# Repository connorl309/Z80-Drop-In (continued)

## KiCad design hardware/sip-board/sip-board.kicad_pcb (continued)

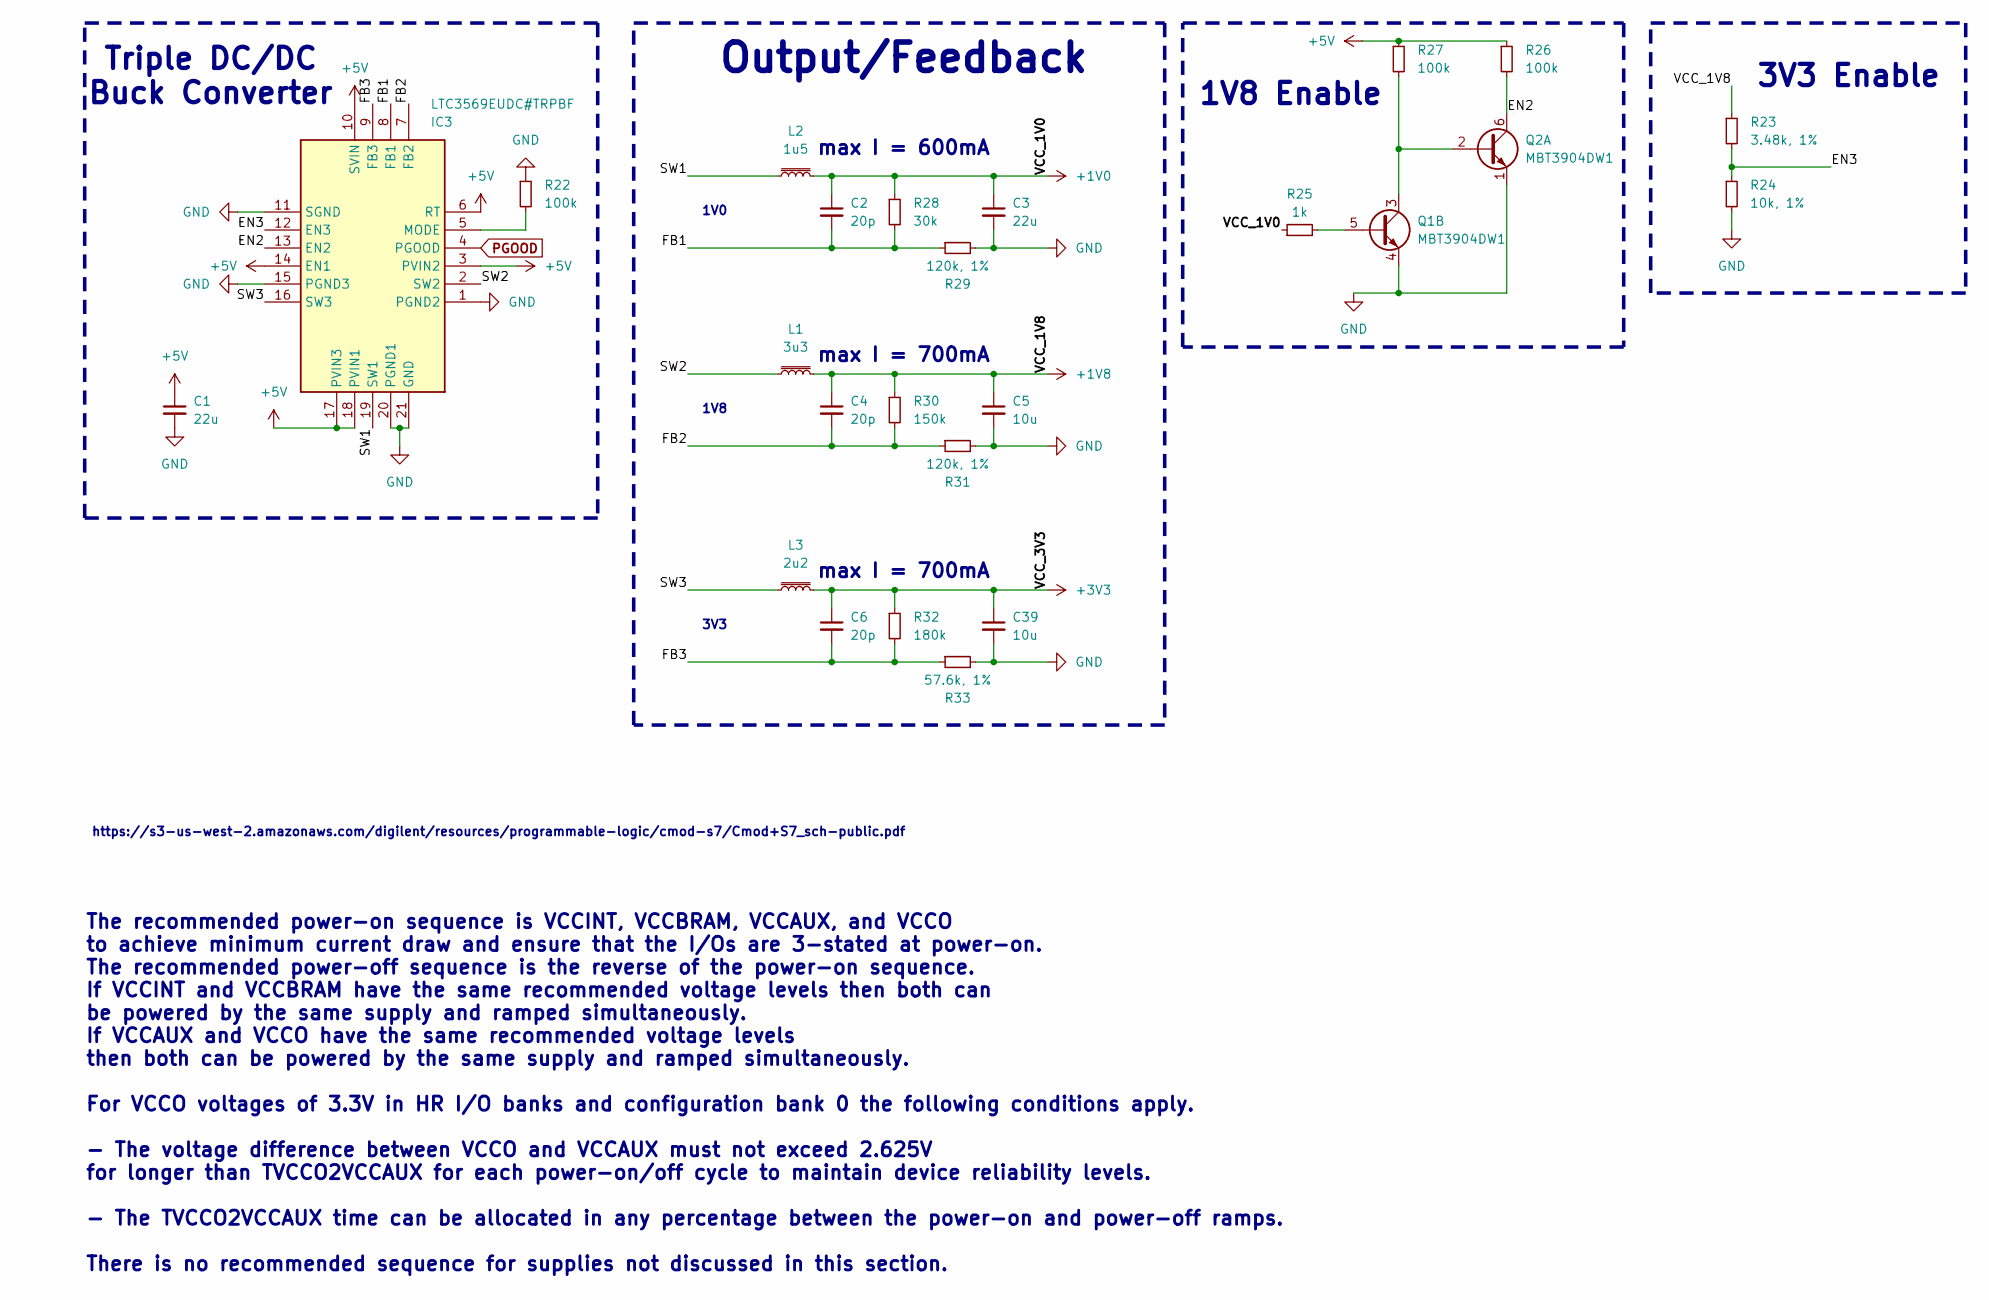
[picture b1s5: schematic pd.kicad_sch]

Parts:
C1, C3: 22u; C_0201_0603Metric
C2, C4, C6: 20p; C_0201_0603Metric
C5, C39: 10u; C_0201_0603Metric
IC3: LTC3569EUDC#TRPBF; QFN50P300X400X80-21N-D; Mouser Part Number 584-LTC3569EUDCTRPBF
L1: 3u3; L_0805_2012Metric; MPN BRC2012T3R3MD
L2: 1u5; L_0805_2012Metric; MPN SRN2012-1R5M
L3: 2u2; L_0805_2012Metric; MPN SRN2012-2R2M
Q1, Q2: MBT3904DW1; SOT-363_SC-70-6
R22, R26, R27: 100k; R_0201_0603Metric
R23: 3.48k, 1%; R_0201_0603Metric
R24: 10k, 1%; R_0201_0603Metric
R25: 1k; R_0201_0603Metric
R28: 30k; R_0201_0603Metric
R29, R31: 120k, 1%; R_0201_0603Metric
R30: 150k; R_0201_0603Metric
R32: 180k; R_0201_0603Metric
R33: 57.6k, 1%; R_0201_0603Metric

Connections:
+1V0: C2.1, C3.1, L2.2, R25.1, R28.1; also elsewhere on the board
+1V8: C4.1, C5.1, L1.2, R23.1, R30.1; also elsewhere on the board
+3V3: C6.1, C39.1, L3.2, R32.1; also elsewhere on the board
+5V: C1.1, IC3.3 (PVIN2), IC3.6 (RT), IC3.10 (SVIN), IC3.14 (EN1), IC3.17 (PVIN3), IC3.18 (PVIN1), R26.1, R27.1; also elsewhere on the board
/Voltage Regulators - 3V3, 1V8, 1V0/EN2: IC3.13 (EN2), Q2.6 (C1), R26.2
/Voltage Regulators - 3V3, 1V8, 1V0/EN3: IC3.12 (EN3), R23.2, R24.1
/Voltage Regulators - 3V3, 1V8, 1V0/FB1: C2.2, IC3.8 (FB1), R28.2, R29.1
/Voltage Regulators - 3V3, 1V8, 1V0/FB2: C4.2, IC3.7 (FB2), R30.2, R31.1
/Voltage Regulators - 3V3, 1V8, 1V0/FB3: C6.2, IC3.9 (FB3), R32.2, R33.1
/Voltage Regulators - 3V3, 1V8, 1V0/SW1: IC3.19 (SW1), L2.1
/Voltage Regulators - 3V3, 1V8, 1V0/SW2: IC3.2 (SW2), L1.1
/Voltage Regulators - 3V3, 1V8, 1V0/SW3: IC3.16 (SW3), L3.1
GND: C1.2, C3.2, C5.2, C39.2, IC3.1 (PGND2), IC3.11 (SGND), IC3.15 (PGND3), IC3.20 (PGND1), IC3.21 (GND), Q1.4 (E2), Q2.1 (E1), R22.1, R24.2, R29.2, R31.2, R33.2; also elsewhere on the board
unnamed: IC3.5 (MODE), R22.2
unnamed: Q1.5 (B2), R25.2
unnamed: Q1.3 (C2), Q2.2 (B1), R27.2
PGOOD: IC3.4 (PGOOD); also elsewhere on the board

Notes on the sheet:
3V3 Enable
max I = 700mA
3V3
Triple DC/DC Buck Converter
The recommended power-on sequence is VCCINT, VCCBRAM, VCCAUX, and VCCO to achieve minimum current draw and ensure that the I/Os are 3-stated at power-on. The recommended power-off sequence is the reverse of the power-on sequence. If VCCINT and VCCBRAM have the same recommended voltage levels then b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
1V0
max I = 600mA
1V8
https://s3-us-west-2.amazonaws.com/digilent/resources/programmable-logic/cmod-s7/Cmod+S7_sch-public.pdf
Output/Feedback
1V8 Enable

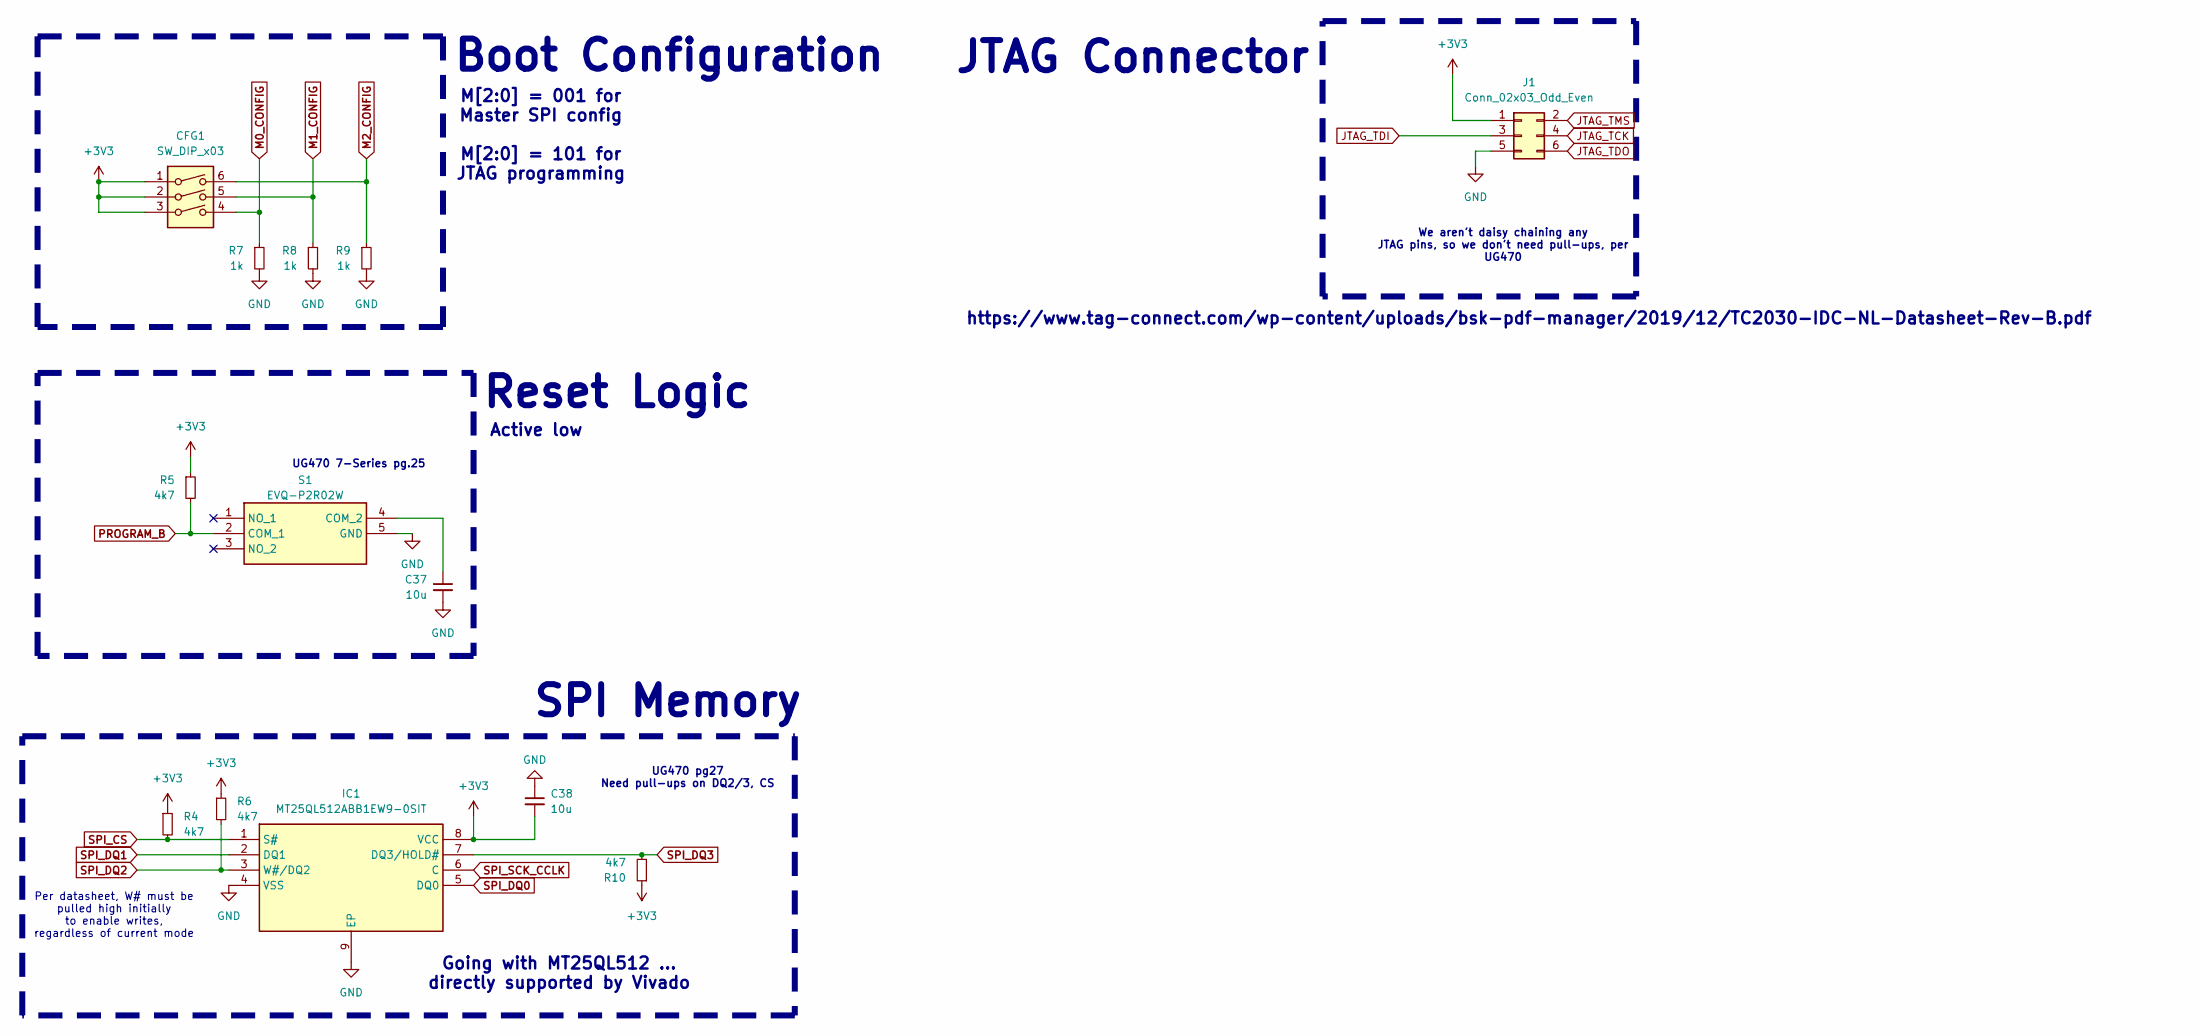
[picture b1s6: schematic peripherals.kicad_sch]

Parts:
C37, C38: 10u; C_0603_1608Metric
CFG1: SW_DIP_x03; WE-3-SPST-DIP
IC1: MT25QL512ABB1EW9-0SIT; Mouser Part Number 340-283908-TRAY
J1: Conn_02x03_Odd_Even; TAG_TC2030-IDC-NL
R4, R5, R6, R10: 4k7; R_0201_0603Metric
R7, R8, R9: 1k; R_0201_0603Metric
S1: EVQ-P2R02W; EVQP2R02W; Mouser Part Number 667-EVQ-P2R02W

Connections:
+3V3: C38.2, CFG1.1, CFG1.2, CFG1.3, IC1.8 (VCC), J1.1, R4.1, R5.1, R6.1, R10.1; also elsewhere on the board
GND: C37.2, C38.1, IC1.4 (VSS), IC1.9 (EP), J1.5, R7.2, R8.2, R9.2, S1.5 (GND); also elsewhere on the board
JTAG_TCK: J1.4; also elsewhere on the board
JTAG_TDI: J1.3; also elsewhere on the board
JTAG_TDO: J1.6; also elsewhere on the board
JTAG_TMS: J1.2; also elsewhere on the board
M0_CONFIG: CFG1.4, R7.1; also elsewhere on the board
M1_CONFIG: CFG1.5, R8.1; also elsewhere on the board
M2_CONFIG: CFG1.6, R9.1; also elsewhere on the board
unnamed: C37.1, S1.4 (COM_2)
PROGRAM_B: R5.2, S1.2 (COM_1); also elsewhere on the board
SPI_CS: IC1.1 (S#), R4.2; also elsewhere on the board
SPI_DQ0: IC1.5 (DQ0); also elsewhere on the board
SPI_DQ1: IC1.2 (DQ1); also elsewhere on the board
SPI_DQ2: IC1.3 (W#/DQ2), R6.2; also elsewhere on the board
SPI_DQ3: IC1.7 (DQ3/HOLD#), R10.2; also elsewhere on the board
SPI_SCK_CCLK: IC1.6 (C); also elsewhere on the board

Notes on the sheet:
Boot Configuration
https://www.tag-connect.com/wp-content/uploads/bsk-pdf-manager/2019/12/TC2030-IDC-NL-Datasheet-Rev-B.pdf
UG470 7-Series pg.25
M[2:0] = 001 for Master SPI config M[2:0] = 101 for JTAG programming
UG470 pg27 Need pull-ups on DQ2/3, CS
Reset Logic
JTAG Connector
Per datasheet, W# must be pulled high initially to enable writes, regardless of current mode
SPI Memory
Going with MT25QL512 ... directly supported by Vivado
Active low
We aren't daisy chaining any JTAG pins, so we don't need pull-ups, per UG470

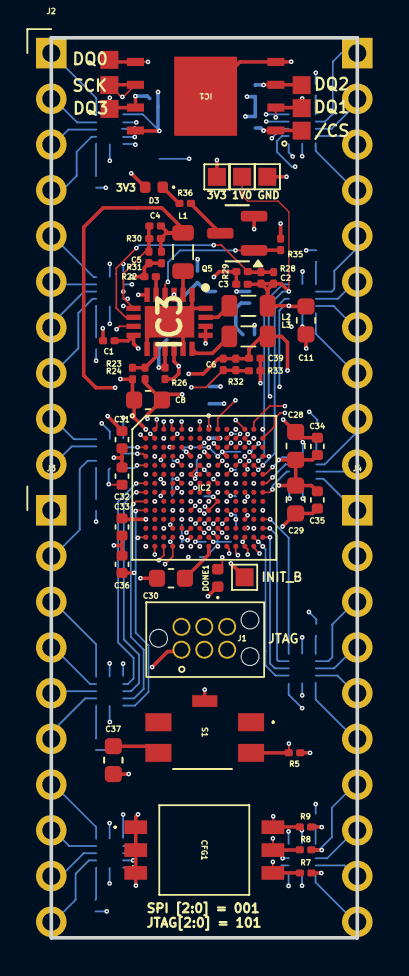
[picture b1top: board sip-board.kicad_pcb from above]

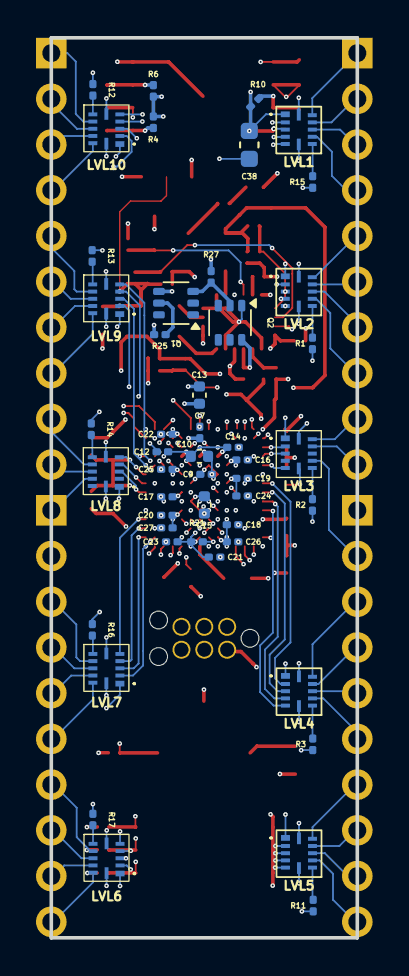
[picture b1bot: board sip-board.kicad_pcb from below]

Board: 10 copper layers, 17.0 x 50.0 mm, 109 parts (48 on the bottom side), 122 nets.

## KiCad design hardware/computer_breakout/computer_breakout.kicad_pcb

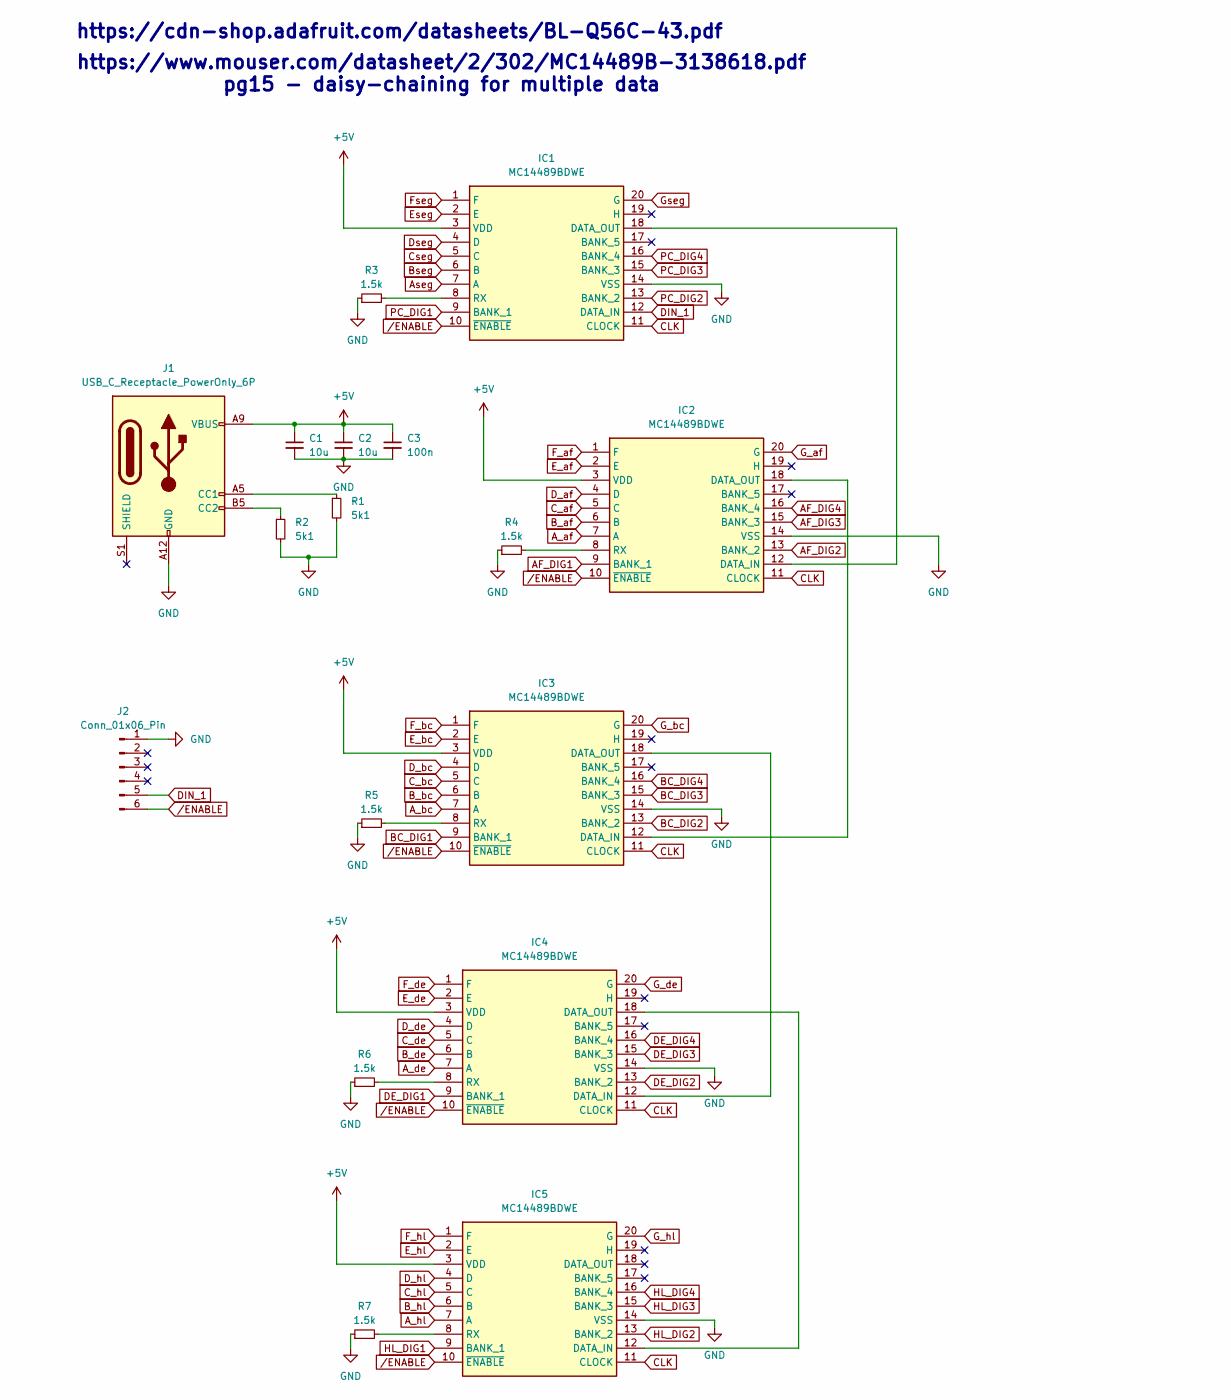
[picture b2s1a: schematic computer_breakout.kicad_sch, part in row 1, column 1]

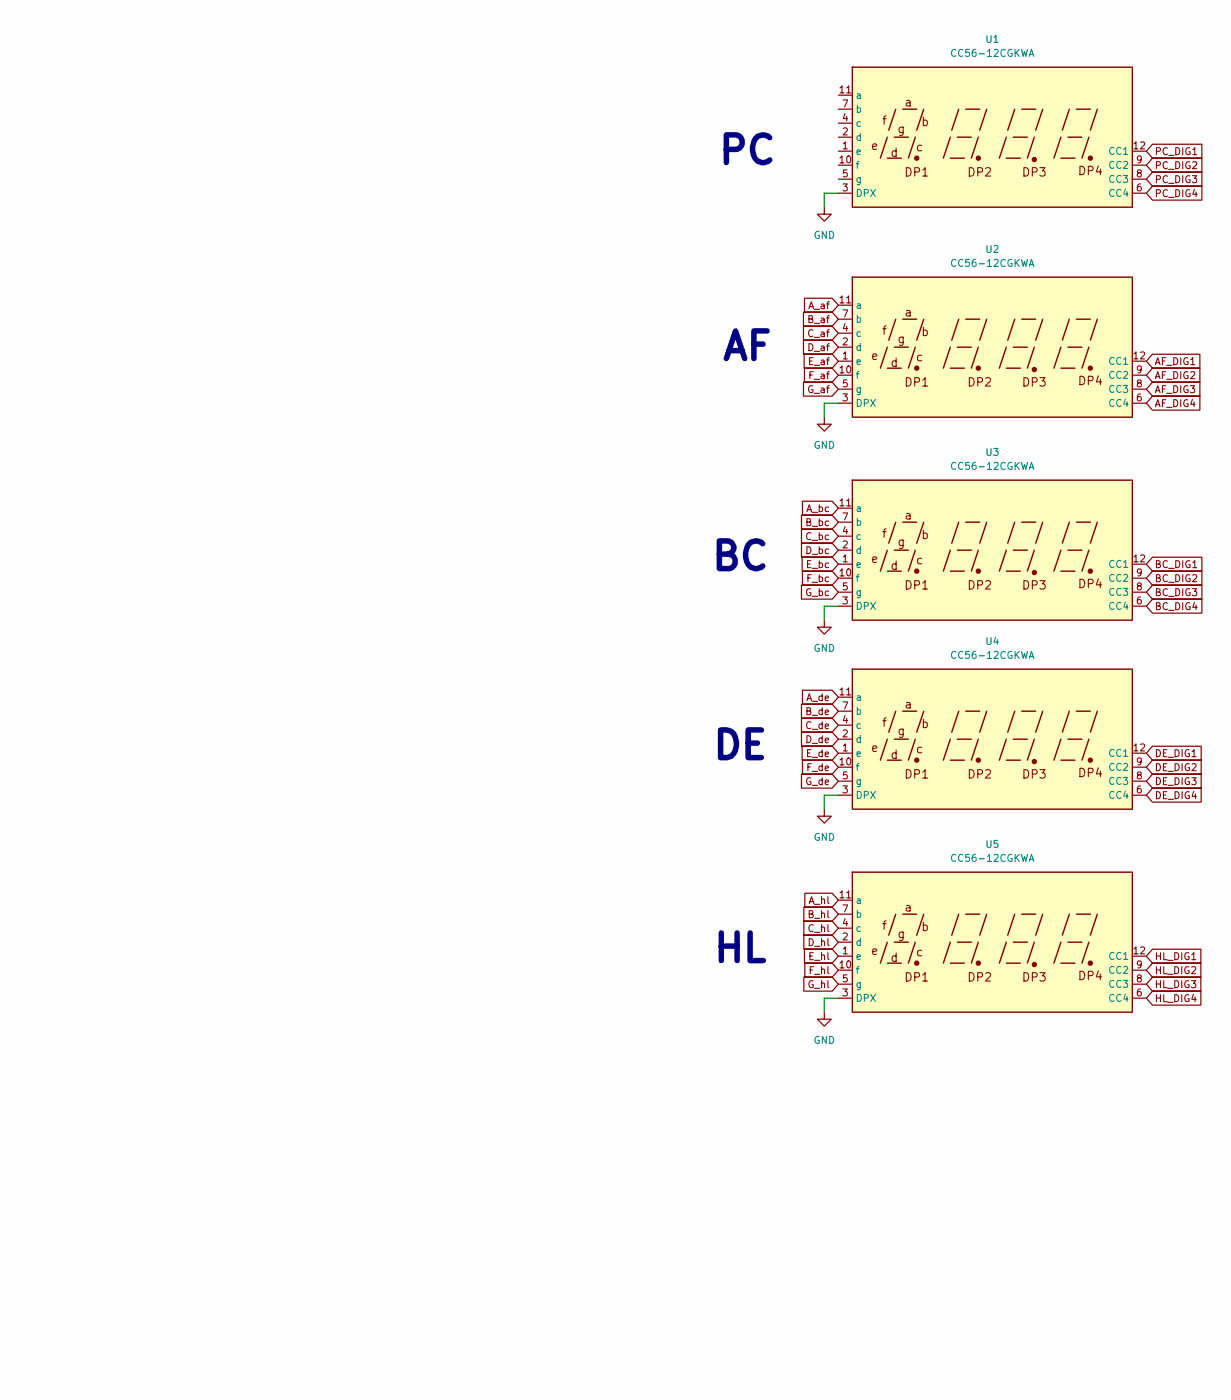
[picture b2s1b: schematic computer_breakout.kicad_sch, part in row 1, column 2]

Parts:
C1, C2: 10u; C_1206_3216Metric_Pad1.33x1.80mm_HandSolder
C3: 100n; C_0603_1608Metric_Pad1.08x0.95mm_HandSolder
IC1, IC2, IC3, IC4, IC5: MC14489BDWE; SOIC127P1030X265-20N; Mouser Part Number 841-MC14489BDWE
J1: USB_C_Receptacle_PowerOnly_6P; USB_C_Receptacle_GCT_USB4110
J2: Conn_01x06_Pin; PinHeader_1x06_P2.54mm_Vertical
R1, R2: 5k1; R_1812_4532Metric_Pad1.30x3.40mm_HandSolder
R3, R4, R5, R6, R7: 1.5k; R_1812_4532Metric_Pad1.30x3.40mm_HandSolder
U1, U2, U3, U4, U5: CC56-12CGKWA; CA56-12CGKWA

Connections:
+5V: C1.1, C2.1, C3.1, IC1.3 (VDD), IC2.3 (VDD), IC3.3 (VDD), IC4.3 (VDD), IC5.3 (VDD), J1.A9 (VBUS), J1.B9 (VBUS)
AF_DIG1: IC2.9 (BANK_1), U2.12 (CC1)
AF_DIG2: IC2.13 (BANK_2), U2.9 (CC2)
AF_DIG3: IC2.15 (BANK_3), U2.8 (CC3)
AF_DIG4: IC2.16 (BANK_4), U2.6 (CC4)
A_af: IC2.7 (A), U2.11 (a)
A_bc: IC3.7 (A), U3.11 (a)
A_de: IC4.7 (A), U4.11 (a)
A_hl: IC5.7 (A), U5.11 (a)
Aseg: IC1.7 (A)
BC_DIG1: IC3.9 (BANK_1), U3.12 (CC1)
BC_DIG2: IC3.13 (BANK_2), U3.9 (CC2)
BC_DIG3: IC3.15 (BANK_3), U3.8 (CC3)
BC_DIG4: IC3.16 (BANK_4), U3.6 (CC4)
B_af: IC2.6 (B), U2.7 (b)
B_bc: IC3.6 (B), U3.7 (b)
B_de: IC4.6 (B), U4.7 (b)
B_hl: IC5.6 (B), U5.7 (b)
Bseg: IC1.6 (B)
CLK: IC1.11 (CLOCK), IC2.11 (CLOCK), IC3.11 (CLOCK), IC4.11 (CLOCK), IC5.11 (CLOCK)
C_af: IC2.5 (C), U2.4 (c)
C_bc: IC3.5 (C), U3.4 (c)
C_de: IC4.5 (C), U4.4 (c)
C_hl: IC5.5 (C), U5.4 (c)
Cseg: IC1.5 (C)
DE_DIG1: IC4.9 (BANK_1), U4.12 (CC1)
DE_DIG2: IC4.13 (BANK_2), U4.9 (CC2)
DE_DIG3: IC4.15 (BANK_3), U4.8 (CC3)
DE_DIG4: IC4.16 (BANK_4), U4.6 (CC4)
DIN_1: IC1.12 (DATA_IN), J2.5
D_af: IC2.4 (D), U2.2 (d)
D_bc: IC3.4 (D), U3.2 (d)
D_de: IC4.4 (D), U4.2 (d)
D_hl: IC5.4 (D), U5.2 (d)
Dseg: IC1.4 (D)
E_af: IC2.2 (E), U2.1 (e)
E_bc: IC3.2 (E), U3.1 (e)
E_de: IC4.2 (E), U4.1 (e)
E_hl: IC5.2 (E), U5.1 (e)
Eseg: IC1.2 (E)
F_af: IC2.1 (F), U2.10 (f)
F_bc: IC3.1 (F), U3.10 (f)
F_de: IC4.1 (F), U4.10 (f)
F_hl: IC5.1 (F), U5.10 (f)
Fseg: IC1.1 (F)
GND: C1.2, C2.2, C3.2, IC1.14 (VSS), IC2.14 (VSS), IC3.14 (VSS), IC4.14 (VSS), IC5.14 (VSS), J1.A12 (GND), J1.B12 (GND), J2.1, R1.2, R2.2, R3.1, R4.1, R5.1, R6.1, R7.1, U1.3 (DPX), U2.3 (DPX), U3.3 (DPX), U4.3 (DPX), U5.3 (DPX)
G_af: IC2.20 (G), U2.5 (g)
G_bc: IC3.20 (G), U3.5 (g)
G_de: IC4.20 (G), U4.5 (g)
G_hl: IC5.20 (G), U5.5 (g)
Gseg: IC1.20 (G)
HL_DIG1: IC5.9 (BANK_1), U5.12 (CC1)
HL_DIG2: IC5.13 (BANK_2), U5.9 (CC2)
HL_DIG3: IC5.15 (BANK_3), U5.8 (CC3)
HL_DIG4: IC5.16 (BANK_4), U5.6 (CC4)
unnamed: IC1.18 (DATA_OUT), IC2.12 (DATA_IN)
unnamed: IC1.8 (RX), R3.2
unnamed: IC2.18 (DATA_OUT), IC3.12 (DATA_IN)
unnamed: IC2.8 (RX), R4.2
unnamed: IC3.18 (DATA_OUT), IC4.12 (DATA_IN)
unnamed: IC3.8 (RX), R5.2
unnamed: IC4.18 (DATA_OUT), IC5.12 (DATA_IN)
unnamed: IC4.8 (RX), R6.2
unnamed: IC5.8 (RX), R7.2
unnamed: J1.A5 (CC1), R1.1
unnamed: J1.B5 (CC2), R2.1
PC_DIG1: IC1.9 (BANK_1), U1.12 (CC1)
PC_DIG2: IC1.13 (BANK_2), U1.9 (CC2)
PC_DIG3: IC1.15 (BANK_3), U1.8 (CC3)
PC_DIG4: IC1.16 (BANK_4), U1.6 (CC4)
/ENABLE: IC1.10 (~ENABLE), IC2.10 (~ENABLE), IC3.10 (~ENABLE), IC4.10 (~ENABLE), IC5.10 (~ENABLE), J2.6

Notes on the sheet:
https://www.mouser.com/datasheet/2/302/MC14489B-3138618.pdf pg15 - daisy-chaining for multiple data
https://cdn-shop.adafruit.com/datasheets/BL-Q56C-43.pdf

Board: 2 copper layers, 22 parts (0 on the bottom side), 64 nets, no tracks yet.

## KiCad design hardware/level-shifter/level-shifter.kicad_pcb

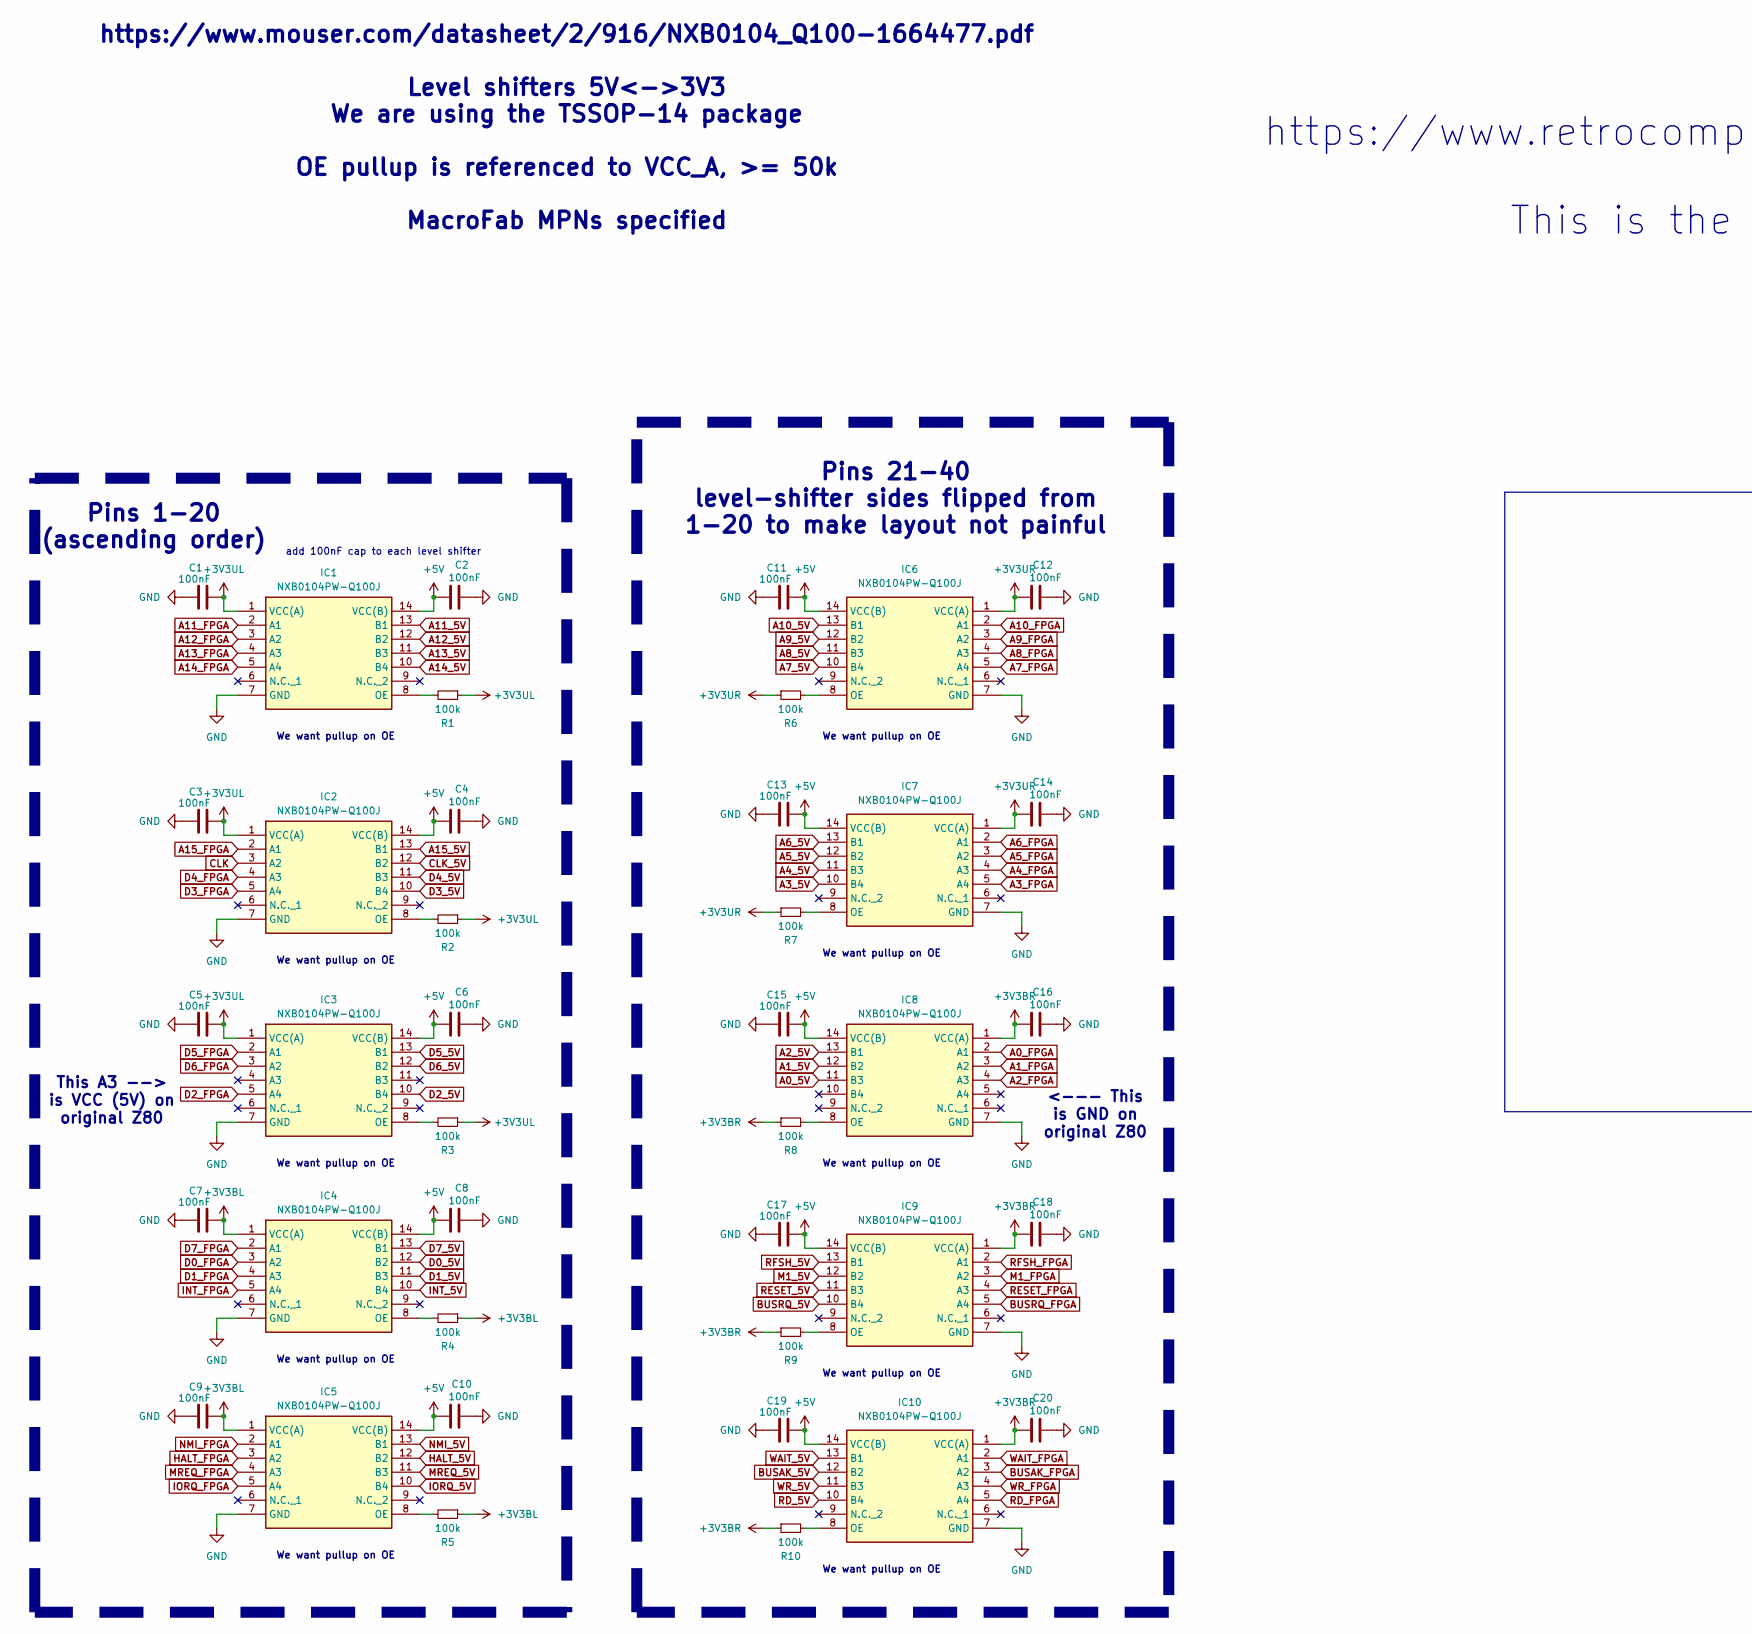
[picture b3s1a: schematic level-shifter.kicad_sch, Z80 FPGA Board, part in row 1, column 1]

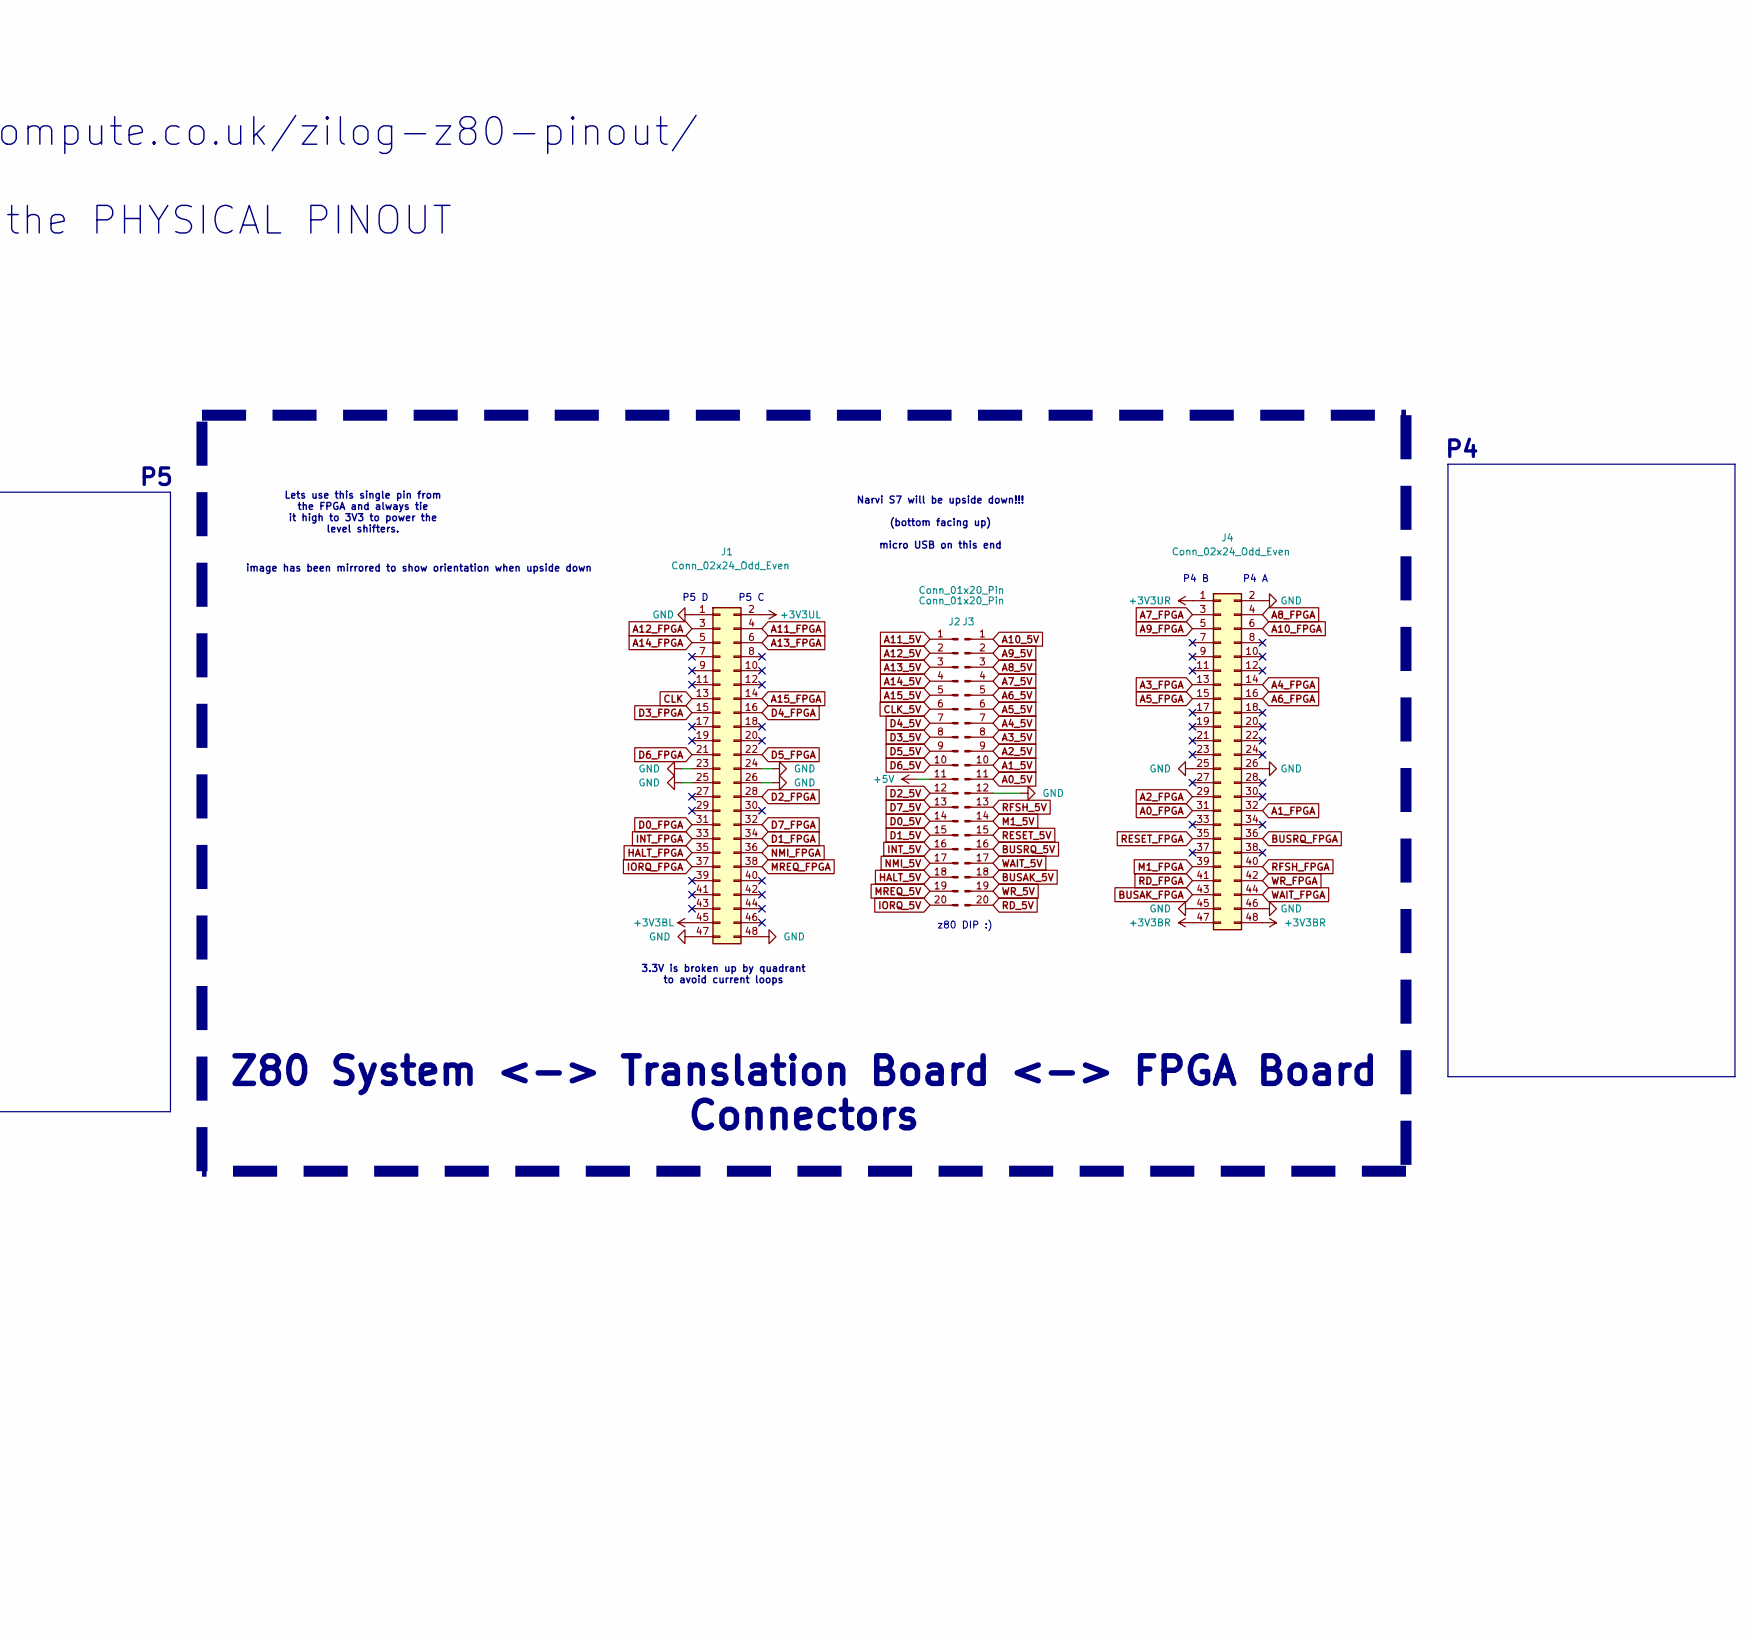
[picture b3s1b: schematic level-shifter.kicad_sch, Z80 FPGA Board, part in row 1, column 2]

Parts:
C1, C2, C3, C4, C5, C6, C7, C8, C9, C10, C11, C12, C13, C14, C15, C16, C17, C18, C19, C20: 100nF; C_0805_2012Metric
IC1, IC2, IC3, IC4, IC5, IC6, IC7, IC8, IC9, IC10: NXB0104PW-Q100J; SOP65P640X110-14N; Mouser Part Number 771-NXB0104PW-Q100J
J1, J4: Conn_02x24_Odd_Even; PinHeader_2x24_P2.54mm_Vertical
J2, J3: Conn_01x20_Pin; PinHeader_1x20_P2.54mm_Vertical
R1, R2, R3, R4, R5, R6, R7, R8, R9, R10: 100k; R_0805_2012Metric; MPN ERJ-UP6D6202V

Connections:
+3V3BL: C7.2, C9.2, IC4.1 (VCC(A)), IC5.1 (VCC(A)), J1.45, R4.1, R5.1
+3V3BR: C16.1, C18.1, C20.1, IC8.1 (VCC(A)), IC9.1 (VCC(A)), IC10.1 (VCC(A)), J4.47, J4.48, R8.1, R9.1, R10.1
+3V3UL: C1.2, C3.2, C5.2, IC1.1 (VCC(A)), IC2.1 (VCC(A)), IC3.1 (VCC(A)), J1.2, R1.1, R2.1, R3.1
+3V3UR: C12.1, C14.1, IC6.1 (VCC(A)), IC7.1 (VCC(A)), J4.1, R6.1, R7.1
+5V: C2.1, C4.1, C6.1, C8.1, C10.1, C11.2, C13.2, C15.2, C17.2, C19.2, IC1.14 (VCC(B)), IC2.14 (VCC(B)), IC3.14 (VCC(B)), IC4.14 (VCC(B)), IC5.14 (VCC(B)), IC6.14 (VCC(B)), IC7.14 (VCC(B)), IC8.14 (VCC(B)), IC9.14 (VCC(B)), IC10.14 (VCC(B)), J2.11
A0_5V: IC8.11 (B3), J3.11
A0_FPGA: IC8.2 (A1), J4.31
A1_5V: IC8.12 (B2), J3.10
A1_FPGA: IC8.3 (A2), J4.32
A2_5V: IC8.13 (B1), J3.9
A2_FPGA: IC8.4 (A3), J4.29
A3_5V: IC7.10 (B4), J3.8
A3_FPGA: IC7.5 (A4), J4.13
A4_5V: IC7.11 (B3), J3.7
A4_FPGA: IC7.4 (A3), J4.14
A5_5V: IC7.12 (B2), J3.6
A5_FPGA: IC7.3 (A2), J4.15
A6_5V: IC7.13 (B1), J3.5
A6_FPGA: IC7.2 (A1), J4.16
A7_5V: IC6.10 (B4), J3.4
A7_FPGA: IC6.5 (A4), J4.3
A8_5V: IC6.11 (B3), J3.3
A8_FPGA: IC6.4 (A3), J4.4
A9_5V: IC6.12 (B2), J3.2
A9_FPGA: IC6.3 (A2), J4.5
A10_5V: IC6.13 (B1), J3.1
A10_FPGA: IC6.2 (A1), J4.6
A11_5V: IC1.13 (B1), J2.1
A11_FPGA: IC1.2 (A1), J1.4
A12_5V: IC1.12 (B2), J2.2
A12_FPGA: IC1.3 (A2), J1.3
A13_5V: IC1.11 (B3), J2.3
A13_FPGA: IC1.4 (A3), J1.6
A14_5V: IC1.10 (B4), J2.4
A14_FPGA: IC1.5 (A4), J1.5
A15_5V: IC2.13 (B1), J2.5
A15_FPGA: IC2.2 (A1), J1.14
BUSAK_5V: IC10.12 (B2), J3.18
BUSAK_FPGA: IC10.3 (A2), J4.43
BUSRQ_5V: IC9.10 (B4), J3.16
BUSRQ_FPGA: IC9.5 (A4), J4.36
CLK: IC2.3 (A2), J1.13
CLK_5V: IC2.12 (B2), J2.6
D0_5V: IC4.12 (B2), J2.14
D0_FPGA: IC4.3 (A2), J1.31
D1_5V: IC4.11 (B3), J2.15
D1_FPGA: IC4.4 (A3), J1.34
D2_5V: IC3.10 (B4), J2.12
D2_FPGA: IC3.5 (A4), J1.28
D3_5V: IC2.10 (B4), J2.8
D3_FPGA: IC2.5 (A4), J1.15
D4_5V: IC2.11 (B3), J2.7
D4_FPGA: IC2.4 (A3), J1.16
D5_5V: IC3.13 (B1), J2.9
D5_FPGA: IC3.2 (A1), J1.22
D6_5V: IC3.12 (B2), J2.10
D6_FPGA: IC3.3 (A2), J1.21
D7_5V: IC4.13 (B1), J2.13
D7_FPGA: IC4.2 (A1), J1.32
GND: C1.1, C2.2, C3.1, C4.2, C5.1, C6.2, C7.1, C8.2, C9.1, C10.2, C11.1, C12.2, C13.1, C14.2, C15.1, C16.2, C17.1, C18.2, C19.1, C20.2, IC1.7 (GND), IC2.7 (GND), IC3.7 (GND), IC4.7 (GND), IC5.7 (GND), IC6.7 (GND), IC7.7 (GND), IC8.7 (GND), IC9.7 (GND), IC10.7 (GND), J1.1, J1.23, J1.24, J1.25, J1.26, J1.47, J1.48, J3.12, J4.2, J4.25, J4.26, J4.45, J4.46
HALT_5V: IC5.12 (B2), J2.18
HALT_FPGA: IC5.3 (A2), J1.35
INT_5V: IC4.10 (B4), J2.16
INT_FPGA: IC4.5 (A4), J1.33
IORQ_5V: IC5.10 (B4), J2.20
IORQ_FPGA: IC5.5 (A4), J1.37
M1_5V: IC9.12 (B2), J3.14
M1_FPGA: IC9.3 (A2), J4.39
MREQ_5V: IC5.11 (B3), J2.19
MREQ_FPGA: IC5.4 (A3), J1.38
NMI_5V: IC5.13 (B1), J2.17
NMI_FPGA: IC5.2 (A1), J1.36
unnamed: IC1.8 (OE), R1.2
unnamed: IC2.8 (OE), R2.2
unnamed: IC3.8 (OE), R3.2
unnamed: IC4.8 (OE), R4.2
unnamed: IC5.8 (OE), R5.2
unnamed: IC6.8 (OE), R6.2
unnamed: IC7.8 (OE), R7.2
unnamed: IC8.8 (OE), R8.2
unnamed: IC9.8 (OE), R9.2
unnamed: IC10.8 (OE), R10.2
RD_5V: IC10.10 (B4), J3.20
RD_FPGA: IC10.5 (A4), J4.41
RESET_5V: IC9.11 (B3), J3.15
RESET_FPGA: IC9.4 (A3), J4.35
RFSH_5V: IC9.13 (B1), J3.13
RFSH_FPGA: IC9.2 (A1), J4.40
WAIT_5V: IC10.13 (B1), J3.17
WAIT_FPGA: IC10.2 (A1), J4.44
WR_5V: IC10.11 (B3), J3.19
WR_FPGA: IC10.4 (A3), J4.42

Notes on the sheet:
https://www.retrocompute.co.uk/zilog-z80-pinout/ This is the PHYSICAL PINOUT
We want pullup on OE
P4 A
P5 C
Z80 System <-> Translation Board <-> FPGA Board Connectors
P5 D
Pins 21-40 level-shifter sides flipped from 1-20 to make layout not painful
z80 DIP :)
3.3V is broken up by quadrant to avoid current loops
image has been mirrored to show orientation when upside down
Narvi S7 will be upside down!!! (bottom facing up) micro USB on this end
https://www.mouser.com/datasheet/2/916/NXB0104_Q100-1664477.pdf Level shifters 5V<->3V3 We are using the TSSOP-14 package OE pullup is referenced to VCC_A, >= 50k MacroFab MPNs specified
add 100nF cap to each level shifter
This A3 --> is VCC (5V) on original Z80
Lets use this single pin from the FPGA and always tie it high to 3V3 to power the level shifters.
<--- This is GND on original Z80
P4 B
Pins 1-20 (ascending order)
